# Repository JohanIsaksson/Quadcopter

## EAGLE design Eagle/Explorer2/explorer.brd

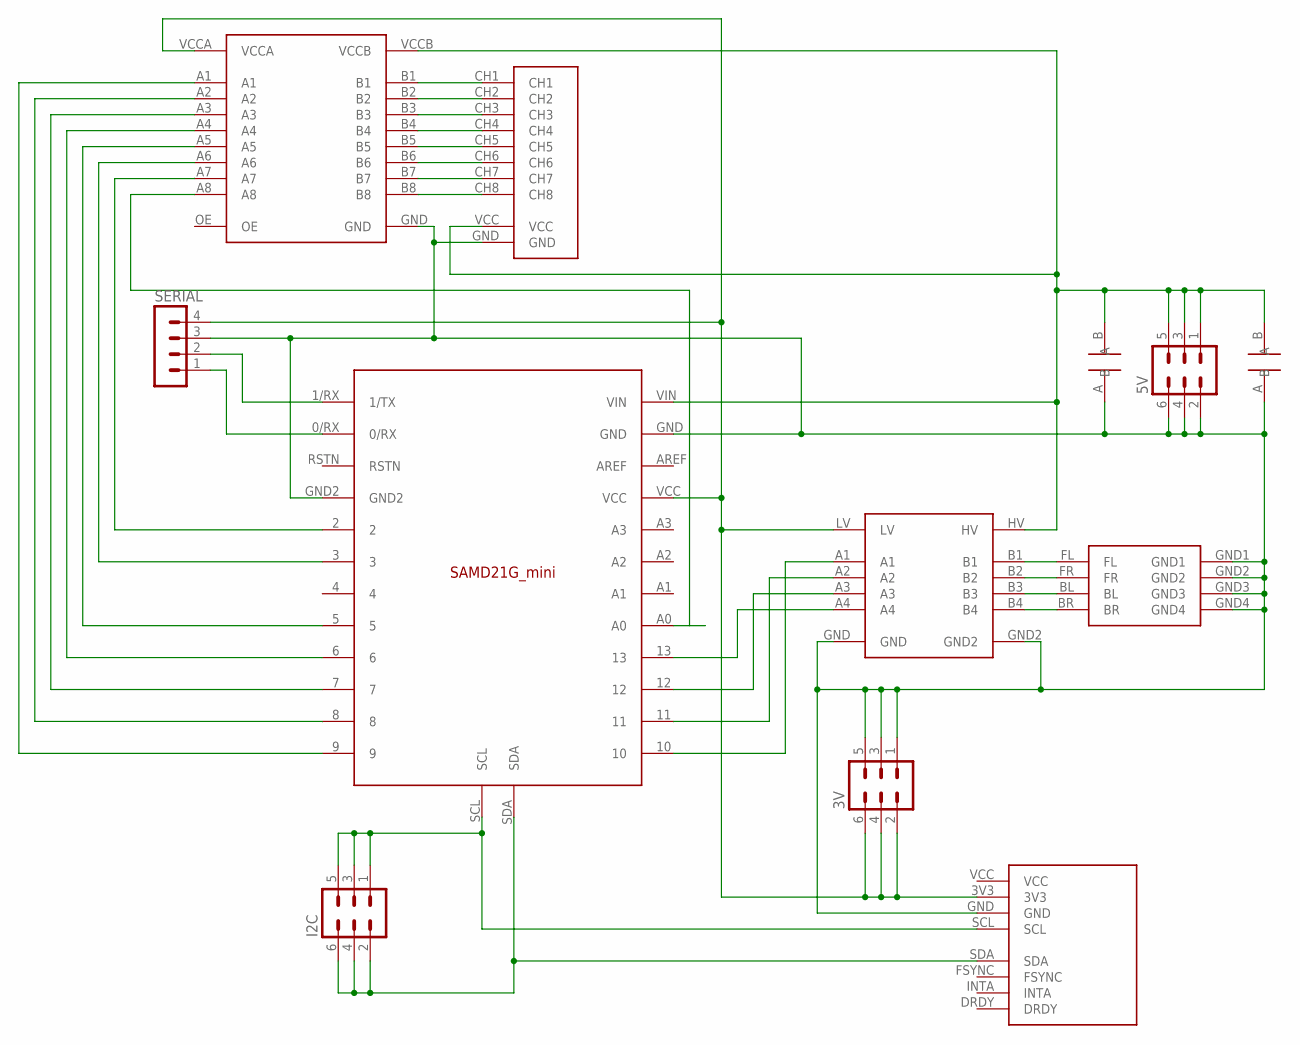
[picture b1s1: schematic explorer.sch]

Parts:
3V, 5V: MA03-2
I2C: MA03-2
SERIAL: MA04-1
U$1: MOTOR_HEADER
U$2, U$7: CAP
U$3: SAMD21G_MINI; SAMD21G-MINI
U$4: LEVELSHIFT_8CH
U$5: LEVELSHIFT_4CH
U$6: RADIO_8CH
U$8: GY-86

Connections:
3V: 3V.2, 3V.4, 3V.6, SERIAL.4, U$3.VCC, U$4.VCCA, U$5.LV, U$8.3V3
5V: 5V.1, 5V.3, 5V.5, U$2.B, U$3.VIN, U$4.VCCB, U$5.HV, U$6.VCC, U$7.B
GND: 3V.1, 3V.3, 3V.5, 5V.2, 5V.4, 5V.6, SERIAL.3, U$1.GND1, U$1.GND2, U$1.GND3, U$1.GND4, U$2.A, U$3.GND, U$3.GND2, U$4.GND, U$5.GND, U$5.GND2, U$6.GND, U$7.A, U$8.GND
unnamed: U$1.BR, U$5.B4
unnamed: U$1.BL, U$5.B3
unnamed: U$1.FR, U$5.B2
unnamed: U$1.FL, U$5.B1
unnamed: U$3.7, U$4.A3
unnamed: U$3.10, U$5.A1
unnamed: U$3.11, U$5.A2
unnamed: U$3.12, U$5.A3
unnamed: U$3.13, U$5.A4
unnamed: U$4.B1, U$6.CH1
unnamed: U$4.B2, U$6.CH2
unnamed: U$4.B3, U$6.CH3
unnamed: U$4.B4, U$6.CH4
unnamed: U$4.B5, U$6.CH5
unnamed: U$4.B6, U$6.CH6
unnamed: U$4.B7, U$6.CH7
unnamed: U$4.B8, U$6.CH8
unnamed: U$3.2, U$4.A7
unnamed: U$3.9, U$4.A1
unnamed: U$3.8, U$4.A2
unnamed: U$3.6, U$4.A4
unnamed: U$3.5, U$4.A5
unnamed: U$3.3, U$4.A6
unnamed: U$3.A0, U$4.A8
unnamed: I2C.1, I2C.3, I2C.5, U$3.SCL, U$8.SCL
unnamed: I2C.2, I2C.4, I2C.6, U$3.SDA, U$8.SDA
unnamed: SERIAL.1, U$3.0/RX
unnamed: SERIAL.2, U$3.1/RX (1/TX)

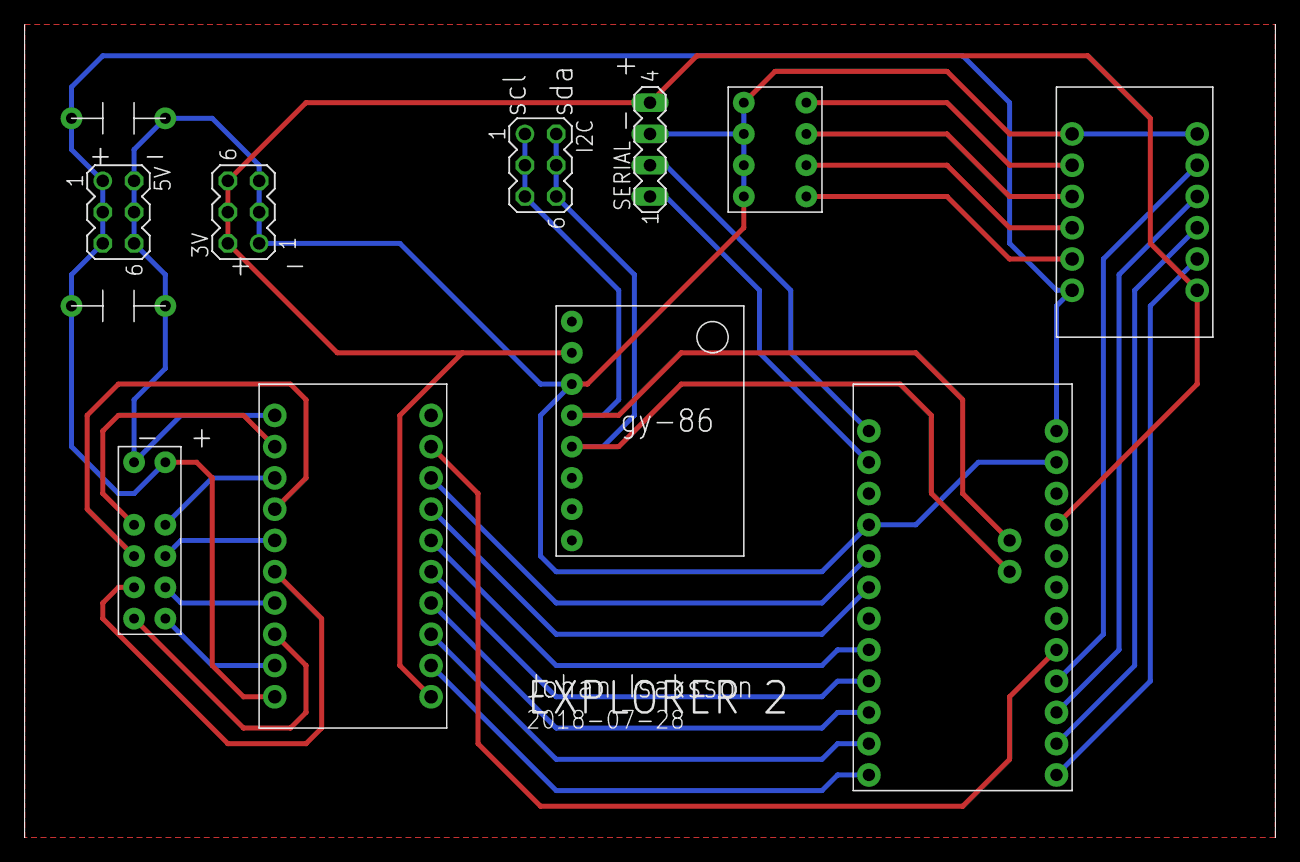
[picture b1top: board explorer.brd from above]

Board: 2 copper layers, 101.6 x 66.0 mm, 12 parts (0 on the bottom side), 31 nets.

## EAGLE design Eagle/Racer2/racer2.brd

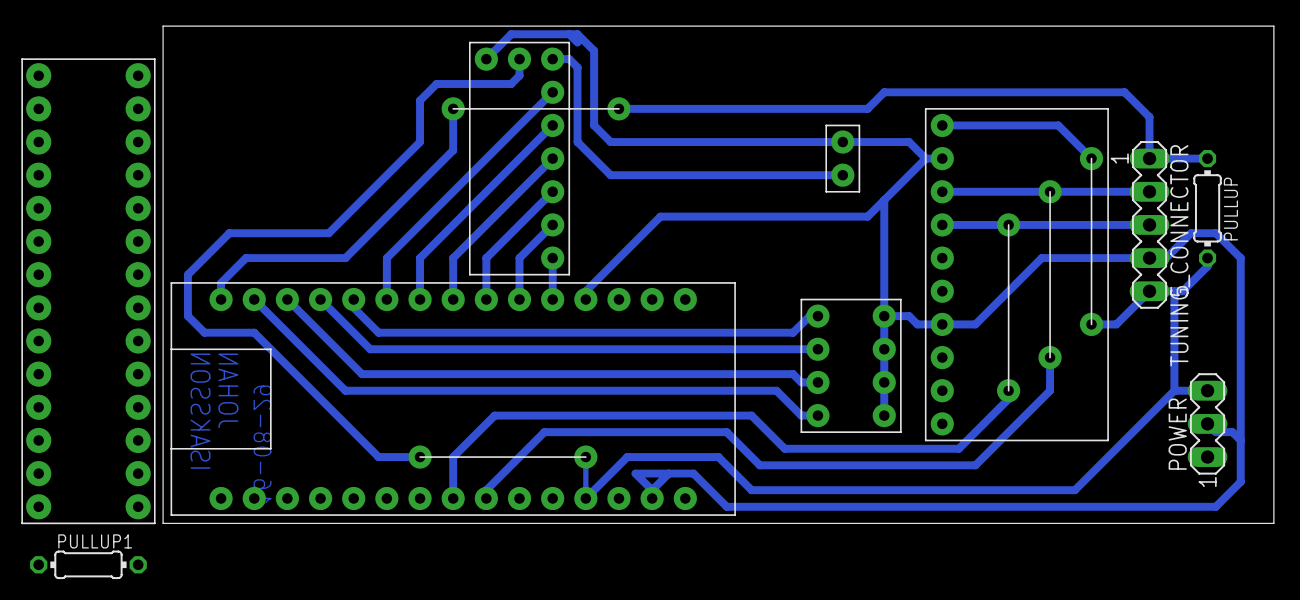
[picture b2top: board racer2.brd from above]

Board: 2 copper layers, 85.1 x 38.1 mm, 15 parts (0 on the bottom side), 22 nets.

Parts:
POWER: MA03-1
PULLUP, PULLUP1: 0204/7
TUNING_CONNECTOR: MA05-1
U$1: NANO
U$2: BUTTON_PULLUP
U$3: FS_RADIO
U$4: MPU9250
U$5: MOTOR_HEADER
U$6, U$7, U$8, U$9, U$10: BRIDGE
U$11: ATMEGA328P

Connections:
5V: POWER.3, PULLUP.2, TUNING_CONNECTOR.5, U$1.5V, U$9.B, U$10.B
GND: POWER.2, TUNING_CONNECTOR.4, U$1.GND, U$1.GND2, U$2.B, U$3.GND, U$4.AD0, U$4.GND, U$5.GND1, U$5.GND2, U$5.GND3, U$5.GND4
unnamed: U$1.D12, U$8.A
unnamed: U$1.A5, U$7.A
unnamed: TUNING_CONNECTOR.3, U$4.SDA, U$6.B
unnamed: U$1.D3, U$3.CH2
unnamed: U$1.D2, U$3.CH1
unnamed: U$1.D4, U$3.CH3
unnamed: U$1.D5, U$3.CH4
unnamed: U$1.D6, U$3.CH5
unnamed: U$1.D7, U$3.CH6
unnamed: U$1.D8, U$5.FL
unnamed: U$1.D9, U$5.FR
unnamed: U$1.D10, U$5.BL
unnamed: U$1.D11, U$5.BR
unnamed: U$2.A, U$3.BAT
unnamed: U$3.VCC, U$9.A
unnamed: PULLUP.1, TUNING_CONNECTOR.1, U$8.B
unnamed: U$1.A4, U$6.A
unnamed: TUNING_CONNECTOR.2, U$4.SCL, U$7.B
unnamed: U$4.VCC, U$10.A
unnamed: PULLUP1.2, U$11.PC6

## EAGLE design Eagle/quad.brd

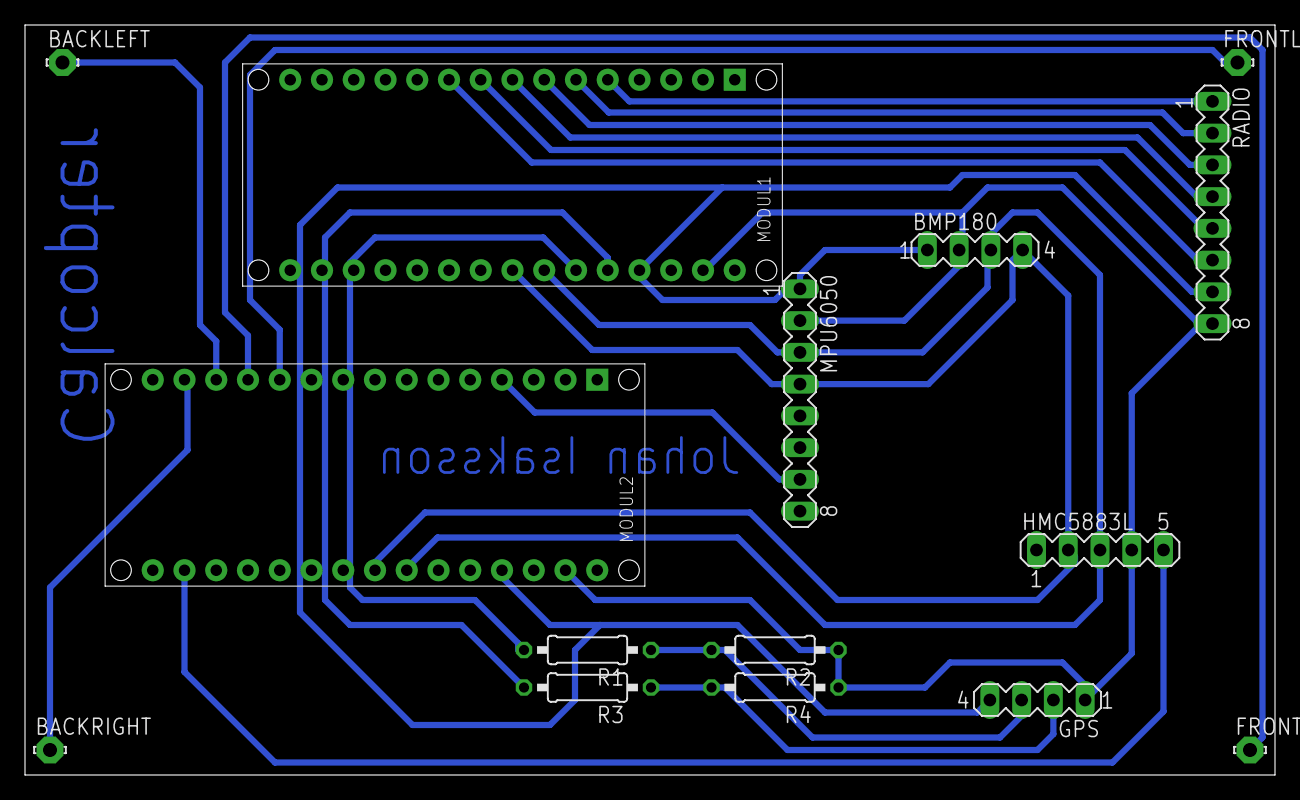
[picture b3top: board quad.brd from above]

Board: 2 copper layers, 100.0 x 60.0 mm, 15 parts (0 on the bottom side), 21 nets.

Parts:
BACKLEFT: LSP11
BACKRIGHT: LSP11
BMP180: MA04-1
FRONTLEFT: LSP11
FRONTRIGHT: LSP11
GPS: MA04-1
HMC5883L: MA05-1
MODUL1, MODUL2: ARDUINO_NANO2
MPU6050: MA08-1
R1, R2, R3, R4: 0207/10
RADIO: MA08-1

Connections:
AREF: MODUL1.J2.13, MODUL2.J2.13
unnamed: FRONTLEFT.MP, MODUL2.J1.11
unnamed: BMP180.1, GPS.4, MODUL1.J2.4, MODUL2.J2.4, MPU6050.1, RADIO.7
unnamed: BACKLEFT.MP, MODUL2.J1.13
unnamed: BACKRIGHT.MP, MODUL2.J1.14
unnamed: MODUL1.J1.5, RADIO.1
unnamed: FRONTRIGHT.MP, MODUL2.J1.12
unnamed: MODUL1.J1.6, RADIO.2
unnamed: MODUL1.J1.7, RADIO.3
unnamed: BMP180.2, GPS.1, HMC5883L.4, MODUL1.J2.2, MODUL2.J1.4, MODUL2.J2.2, MPU6050.2, MPU6050.7, R2.1, R4.1, RADIO.8
unnamed: MODUL1.J2.6, R1.2
unnamed: MODUL1.J1.8, RADIO.4
unnamed: MODUL1.J1.9, RADIO.5
unnamed: MODUL1.J1.10, RADIO.6
unnamed: HMC5883L.5, MODUL2.J2.14
unnamed: BMP180.3, HMC5883L.3, MODUL1.J2.7, MODUL2.J2.7, MPU6050.3
unnamed: BMP180.4, HMC5883L.2, MODUL1.J2.8, MODUL2.J2.8, MPU6050.4
unnamed: MODUL1.J2.5, R3.2
unnamed: GPS.3, R1.1, R2.2
unnamed: GPS.2, R3.1, R4.2
VIN: MODUL1.J2.1, MODUL2.J2.1

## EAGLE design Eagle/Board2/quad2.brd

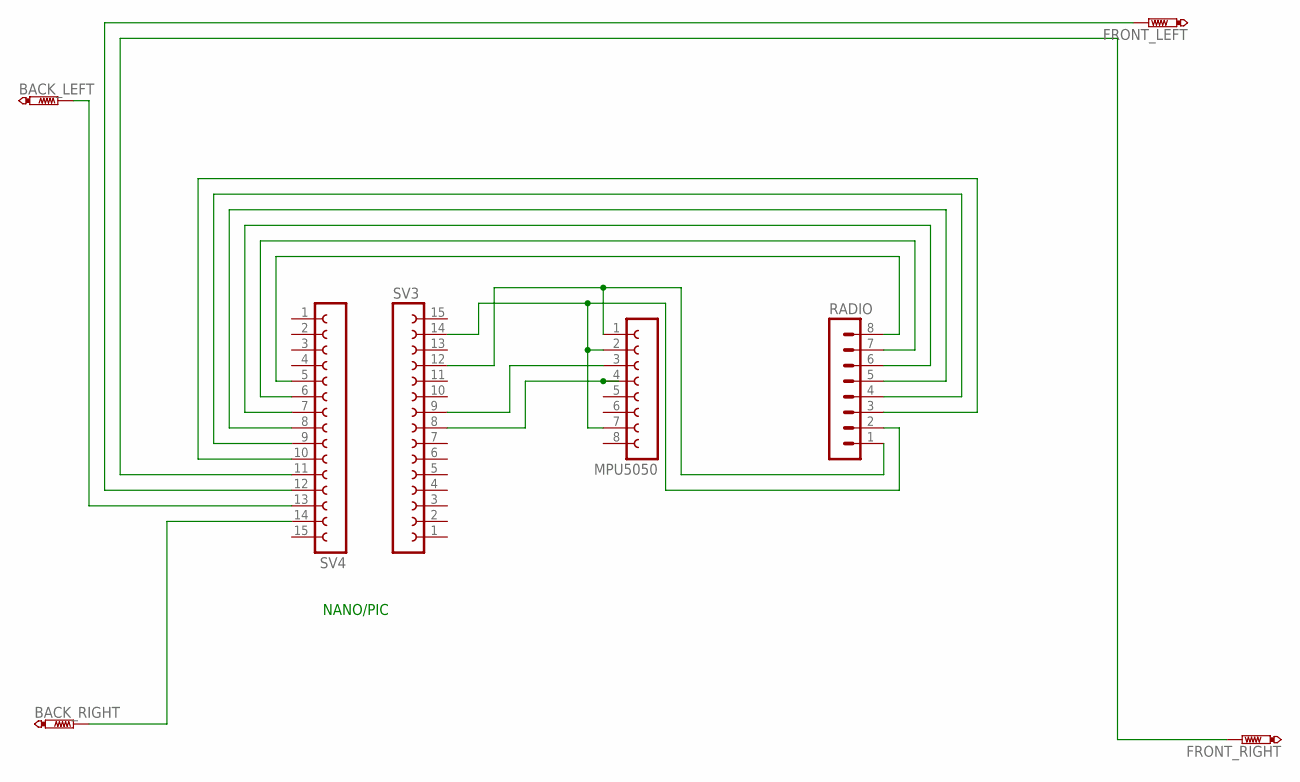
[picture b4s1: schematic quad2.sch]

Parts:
BACK_LEFT: PTR1PAD1-13Y; P1-13Y
BACK_RIGHT: PTR1PAD1-13Y; P1-13Y
FRONT_LEFT: PTR1PAD1-13Y; P1-13Y
FRONT_RIGHT: PTR1PAD1-13Y; P1-13Y
MPU5050: FE08-1; FE08
RADIO: MA08-1
SV3, SV4: FE15-1; FE15

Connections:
unnamed: MPU5050.1, RADIO.1, SV3.12
unnamed: RADIO.4, SV4.9
unnamed: MPU5050.2, MPU5050.7, RADIO.2, SV3.14
unnamed: RADIO.5, SV4.8
unnamed: MPU5050.3, SV3.9
unnamed: MPU5050.4, SV3.8
unnamed: RADIO.6, SV4.7
unnamed: RADIO.3, SV4.10
unnamed: RADIO.7, SV4.6
unnamed: RADIO.8, SV4.5
unnamed: BACK_RIGHT.TP, SV4.14
unnamed: BACK_LEFT.TP, SV4.13
unnamed: FRONT_LEFT.TP, SV4.12
unnamed: FRONT_RIGHT.TP, SV4.11

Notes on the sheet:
NANO/PIC

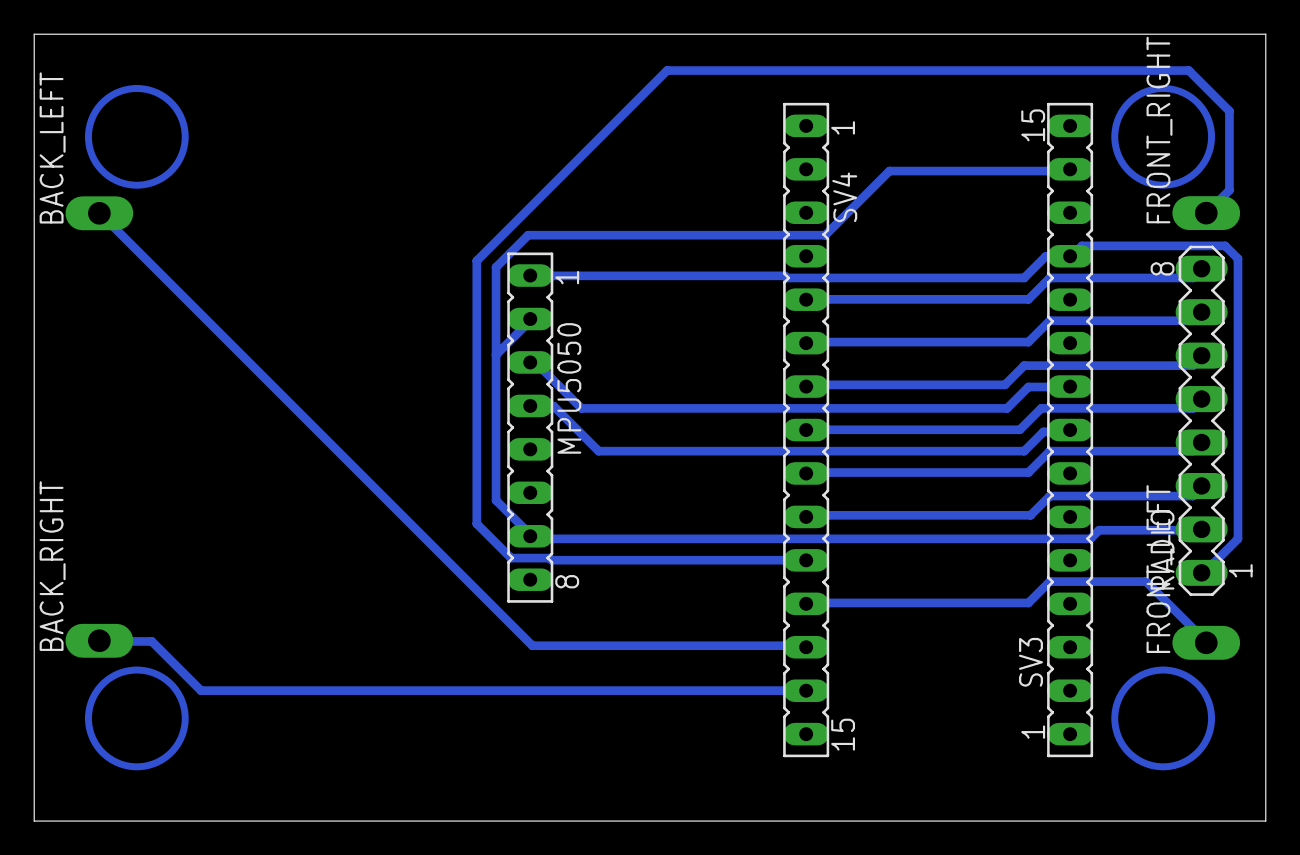
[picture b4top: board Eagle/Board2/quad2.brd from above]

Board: 2 copper layers, 72.0 x 46.0 mm, 8 parts (0 on the bottom side), 14 nets.

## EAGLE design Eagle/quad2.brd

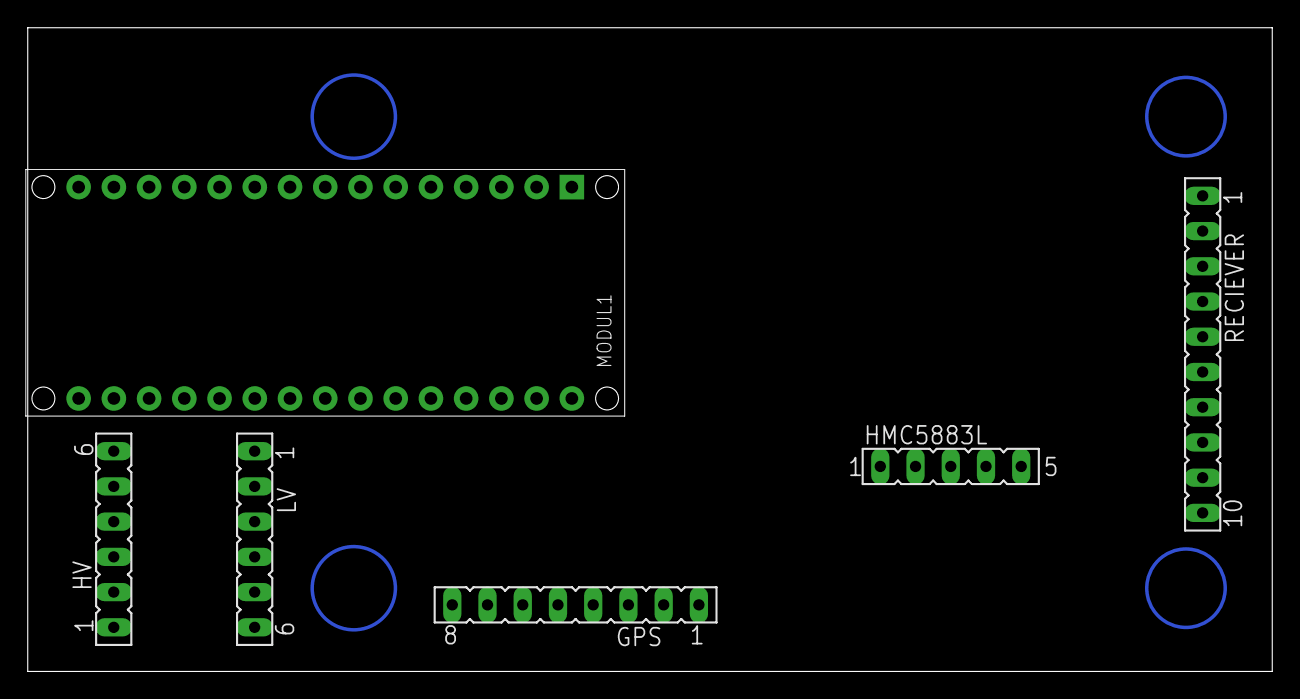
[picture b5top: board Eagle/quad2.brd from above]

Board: 2 copper layers, 89.7 x 46.4 mm, 6 parts (0 on the bottom side), 19 nets, no tracks yet.

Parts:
GPS: FE08
HMC5883L: FE05-1
HV: FE06
LV: FE06
MODUL1: ARDUINO_NANO2
RECIEVER: FE10

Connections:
unnamed: MODUL1.J1.11, RECIEVER.1
unnamed: GPS.5, HV.3, MODUL1.J2.4, RECIEVER.8
unnamed: GPS.8, MODUL1.J1.13
unnamed: GPS.7, MODUL1.J1.14
unnamed: MODUL1.J1.5, RECIEVER.2
unnamed: MODUL1.J1.12, RECIEVER.10
unnamed: MODUL1.J1.6, RECIEVER.3
unnamed: MODUL1.J1.7, RECIEVER.4
unnamed: GPS.2, HMC5883L.4, HV.4, LV.3, MODUL1.J2.2, RECIEVER.9
unnamed: GPS.3, LV.1
unnamed: MODUL1.J1.8, RECIEVER.5
unnamed: MODUL1.J1.9, RECIEVER.6
unnamed: MODUL1.J1.10, RECIEVER.7
unnamed: HMC5883L.5, LV.4, MODUL1.J2.14
unnamed: HV.5, MODUL1.J2.5
unnamed: HMC5883L.3, MODUL1.J2.7
unnamed: HMC5883L.2, MODUL1.J2.8
unnamed: HV.6, MODUL1.J2.6
unnamed: GPS.4, LV.2

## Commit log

2015-06-12 Projektplan och mappar.
2015-06-12 Projektplan klar.
2015-06-15 Added untested files.
2015-06-16 Multiple-def problem...
2015-06-16 Lade till copter.ino.
2015-06-17 Komplementarfilter implementerat.
2015-06-18 Lade till regleringsbibliotek.
2015-06-18 PID-reglering.
2015-06-22 Fixed acc offsets and added maximum to pid.
2015-06-23 Pid klar. Motorkalibreringsfil klar.
2015-06-24 Fixade stuff.
2015-06-25 Kommenterade kod.
2015-06-27 Bytte till mer beskrivande namn, gyro->imu.
2015-06-27 Skrev magnetometerkod.
2015-06-29 Magnetometer integrerad.
2015-07-02 Testade yaw-integreringen, funkade inte alls.
2015-07-10 Skrev lite yaw-pid.
2015-07-27 Bytte till arctan vid berakning av accelerometervinkel.
2015-07-27 Lade till testfil fr ultraljudssensor.
2015-07-27 English from nom on. Reduced P-, increased D-regulator.
2015-07-30 Calibrated gyro to rad/s scale.
2015-07-30 Added testfile.
2015-07-31 Added failsafe if connection lost.
2015-08-16 Added temporary yaw-regulation.
2015-08-16 Fixed folder structure.
2015-09-01 PID adjustments, height estimation and more.
2015-09-03 Small fix.
2015-09-03 PID parma testing.
2015-09-11 More pid param testing, mag code and reduced maximum ref angles.
2015-09-20 Removed MPU6050 library.
2015-11-16 Optimized code.
2015-11-30 Removed servo library. Shit works. Started on eaglecad design of pcb.
2015-12-30 Added acrobtic mode. Not tested yet.
2015-12-31 Fixed new pid for acro mode.
2016-01-03 PID for acrobatic mode is done. Flying smooth now.
2016-01-03 Forgot to set one pid constant.
2016-01-11 Cleaned up pid code and added integral part for yaw stabilization.
2016-01-24 Added some eagle files. Small copter board is complete.
2016-01-24 Added some eagle files. Small copter board is complete. again.
2016-01-27 Power distribution board is completed.
2016-01-28 Worked on board for the large quad.
2016-01-28 Large board done
2016-03-07 Simplified large board. Planning to put distance sensors on a separate board.
2016-03-10 Fixed trace width.
2016-03-11 Final board design and added ground fill.
2016-03-11 Rotated print.
2016-03-12 Split up code for both modules on the large quad.
2016-03-18 Trade-off with I2C to fix delay on radio interrupt.
2016-03-21 Optimized protocol between modules to enhance refresh rate.
2016-06-14 Fixed pid parameters for large quad and started on height controller.
2016-06-19 Reduced yaw p gain.
2016-07-02 Added kalman filter for altitude estimation, added matrix library and started on barometer communication.
2016-07-02 Finished barometer reading procedure.
2016-07-03 Fixed matrix library, now with operator overloading.
2016-07-05 Updated PID code.
2016-07-09 Small fixes to barometer reading.
2016-07-27 Minor changes to small quad tuning.
2016-07-31 Started working on new racequad schematic.
2016-08-05 Started on new racequad code. +New stability controller.
2016-08-14 Changed structure of imu code.
2016-08-14 Implemented eeprom storing.
2016-09-20 Added tuning mode.
2016-09-28 Fixed horizon mode and implemented exponential joystick rate.
2016-09-30 Updated.
2016-10-01 Fixed bug in radio channel.
2016-10-04 Optimized low pass filter.
2017-03-15 Started on new Explorer code.
2017-03-16 Updated imu for Explorer2.
2017-03-16 Readded failsafe mechanisms.
2017-03-16 Fixed radio control and esc pulse generation for Explorer2.
2017-09-30 Finished Explorer 2 schematic and board design.
2018-01-11 Cleaned up Explorer2 main code and updated IMU.
2018-01-11 Fixed compililation errors. DMP is not functioning satisfatory.
2018-01-11 Removed DMP and readded old code for accessing sensor registers.
2018-01-12 Fixed compilation errors, attachInterrupt has stopped working.
2018-01-12 Added more MPU9250 inits.
2018-01-15 Managed to get BMP180 working. MPU9250 accelerometer still not working.
2018-01-16 Switched back to MPU6050 sensor (again). YPR and barometer altitude is now functioning.
2018-01-17 Cleaned up imu code and removed dynamic memory allocation from the matrix library.
2018-01-20 Rewrote matrix lib and kalman to not use dynamic memory.
2018-01-20 Fixed compile errors in kalman filter.
2018-01-21 Fixed a bug in matrix inversion and added a missing transpose in kalman filter.
2018-01-22 Fixed matrix transpose function and updated matrix test.
2018-01-23 Fixed matrix sizes and added kalman filter test.
2018-02-20 Fixed motor signal generation and radio receiver interrupts. Something wrong with pin 8 (pitch), chip may be faulty.
2018-04-15 Redesigned Explorer2 board to use two copper layers. Cleaned up and tested Explorer2 code, ready for test.
2018-07-25 Replaced all sensor breakout boards with one gy-86 board. Started on pids for altitude hold.
2018-07-25 Added functionality for ascending and descending in altitude hold mode.
2018-07-26 Implemented the interface for MS5611 and got it working. Must redo the kalman filter for the new sensor.
2018-08-01 Fixed MS5611 pressure conversion.
2018-12-08 Removed pwm radio interface and switched to sbus.
2019-07-15 Tests with fraction data type.
2019-10-20 Code cleanup. New class sbus decoding.
2019-10-26 Motor signals are now generated using hardware timers. I2C issue detected, SERCOM module hangs on data request. Clock noise can be the issue.
2019-11-01 Replaced arduino I2C library with specilaized lib for samd21.
